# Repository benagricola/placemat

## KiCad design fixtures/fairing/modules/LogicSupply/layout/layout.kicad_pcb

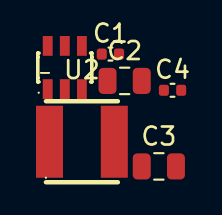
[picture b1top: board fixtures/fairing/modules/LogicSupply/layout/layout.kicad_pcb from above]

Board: 2 copper layers, 6 parts (0 on the bottom side), 5 nets, no tracks yet.

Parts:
C1, C4: GCM155R71H104KE02D; C_0402_1005Metric
C2: GMC21X5R106M50NT; C_0805_2012Metric
C3: CL21A226MOQNNNE; C_0805_2012Metric
U1: AP63203WU-7; TSOT-26_L2.9-W1.6-P0.95-LS2.8-BL
U2: SMNR4020-2.2UH; IND-SMD_L4.0-W4.0_LQH44PN2R2MP0L

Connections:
BST_3V3: C4.1, U1.6
GND: C1.2, C2.2, C3.2, U1.4
SW_3V3: C4.2, U1.5, U2.1
V3V3: C3.1, U1.1, U2.2
VSHUNT: C1.1, C2.1, U1.2, U1.3

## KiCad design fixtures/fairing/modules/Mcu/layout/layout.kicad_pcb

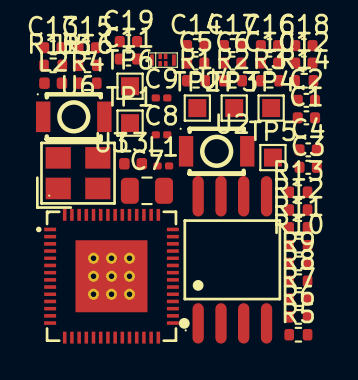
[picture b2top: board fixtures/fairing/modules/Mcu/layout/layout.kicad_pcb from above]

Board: 2 copper layers, 50 parts (0 on the bottom side), 32 nets, no tracks yet.

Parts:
C1, C2, C3: 1pF 50V C0G; C_0402_1005Metric
C4, C6, C10, C12, C13, C17: GCM155R71H104KE02D; C_0402_1005Metric
C5, C11, C14, C16: CL05A105KO5NNND; C_0402_1005Metric
C7: GRM21BC81E106KE51L; C_0805_2012Metric
C8, C9: GRM0335C2A1R5CA01D; C_0201_0603Metric
C15: GCM155R71H103KA55D; C_0402_1005Metric
C18, C19: GCM1555C1H160JA16D; C_0402_1005Metric
L1: 2.4nH; L_0201_0603Metric
L2: LQG15HS2N0S02D; L_0402_1005Metric
L3: 24nH; L_0402_1005Metric
R1, R4, R6, R7, R9, R10: ERJ-2GE0R00X; R_0402_1005Metric
R2, R3, R5, R8, R11, R12, R13, R14, R15: ERJ-2RKF1002X; R_0402_1005Metric
R16: ERJ-2RKF4990X; R_0402_1005Metric
TP1, TP2, TP3, TP4, TP5, TP6: ?; TestPoint_Pad_1.0x1.0mm
U1: ANT016008LCS2442MA1; ANT-SMD_6P-L1.6-W0.8-P1.20-1
U2: W25Q64JVSSIQ; SOIC-8_L5_3-W5_3-P1_27-LS8_0-BL
U3: ESP32-S3R8; QFN-56_L7_0-W7_0-P0_40-TL-EP4_0
U4, U5: B3U-1000P; KEY-SMD_B3U-1000PM
U6: S3240000101040; CRYSTAL-SMD_4P-L3_2-W2_5-BL

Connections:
ANT24_FEED: C3.1, R1.2, U1.4
ANT24_RAD: C1.1, U1.1
BOOT_STRAP: R2.2, TP2.1, U3.5, U4.1
FLASH_CLK: R4.2, U2.6
FLASH_CLK_CHIP: R4.1, U3.33
FLASH_CS: R5.2, U2.1, U3.32
FLASH_D: R6.2, U2.5
FLASH_D_CHIP: R6.1, U3.35
FLASH_HD: R7.2, R8.2, U2.7
FLASH_HD_CHIP: R7.1, U3.30
FLASH_Q: R9.2, U2.2
FLASH_Q_CHIP: R9.1, U3.34
FLASH_WP: R10.2, R11.2, U2.3
FLASH_WP_CHIP: R10.1, U3.31
GND: C1.2, C2.2, C3.2, C4.2, C5.2, C6.2, C7.2, C8.2, C9.2, C10.2, C11.2, C12.2, C13.2, C14.2, C15.2, C16.2, C17.2, C18.2, C19.2, R12.2, R14.2, R15.2, TP3.1, U2.4, U3.57, U4.2, U5.2, U6.2, U6.4
MCU_EN: C5.1, R3.2, TP4.1, U3.4, U5.1
RF_50: C2.1, C8.1, L1.2, R1.1
RF_CHIP: C9.1, L1.1, U3.1
SLOT_RUN: R12.1, U3.11
STRAP_DOWNLOAD: R15.1, U3.52
STRAP_JTAG: R13.2, U3.8
STRAP_VSPI: R14.1, U3.51
UART_RX: TP5.1, U3.50
UART_TX: R16.2, TP6.1
UART_TX_CHIP: R16.1, U3.49
V3V3: C4.1, C7.1, C11.1, C12.1, C13.1, C14.1, C15.1, L2.1, R2.1, R3.1, R13.1, TP1.1, U3.20, U3.46, U3.55, U3.56
VDD_RF: C10.1, L2.2, U3.2, U3.3
VDD_SPI: C6.1, C16.1, C17.1, R5.1, R8.1, R11.1, U2.8, U3.29
XTAL_1: C18.1, L3.2, U6.1
XTAL_N: C19.1, U3.53, U6.3
XTAL_P: L3.1, U3.54
ant24.Dummy_pad: U1.2, U1.3, U1.5, U1.6

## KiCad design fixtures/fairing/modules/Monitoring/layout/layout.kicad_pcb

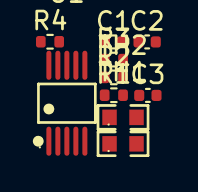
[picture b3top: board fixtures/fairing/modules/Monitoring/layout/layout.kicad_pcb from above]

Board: 2 copper layers, 10 parts (0 on the bottom side), 6 nets, no tracks yet.

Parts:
C1, C2, C3: GCM155R71H104KE02D; C_0402_1005Metric
R1, R3: ERJ-2RKF4702X; R_0402_1005Metric
R2, R4: ERJ-2RKF1001X; R_0402_1005Metric
TH1, TH2: NCU18XH103F60RB; R0603
U1: ADS1115IDGSR; MSOP-10_L3_0-W3_0-P0_50-LS5_0-BL

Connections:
ADC_BUCK: C2.1, R2.2, U1.6
ADC_PD: C3.1, R4.2, U1.7
GND: C1.2, C2.2, C3.2, TH1.2, TH2.2, U1.3
NTC_BUCK: R1.2, R2.1, TH1.1
NTC_PD: R3.2, R4.1, TH2.1
V3V3: C1.1, R1.1, R3.1, U1.1, U1.8

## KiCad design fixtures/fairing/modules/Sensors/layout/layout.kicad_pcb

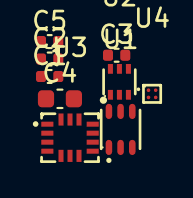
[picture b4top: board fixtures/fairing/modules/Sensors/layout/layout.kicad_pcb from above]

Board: 2 copper layers, 9 parts (0 on the bottom side), 4 nets, no tracks yet.

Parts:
C1, C2, C3, C5: GCM155R71H104KE02D; C_0402_1005Metric
C4: CL10A475KO8NNNC; C_0603_1608Metric
U1: LTR-303ALS-01; TDFN-6_L2.0-W2.0-P0.65-BL
U2: TMP102AIDRLR(UMW); SOT-563_L1.6-W1.2-P0.50-LS1.6-BL
U3: LSM6DS3TR-C; LGA-14_L3.0-W2.5-P0.50-TL
U4: MMC5603NJ; FLIPCHIP-4_L0.8-W0.8-R2-C2-P0.40-TL

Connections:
GND: C1.2, C2.2, C3.2, C4.2, C5.2, U1.3, U2.2, U2.4, U3.1, U3.2, U3.3, U3.6, U3.7, U4.A1
SCL: U1.4, U3.13, U4.A2
SDA: U1.6, U3.14, U4.B2
V3V3: C1.1, C2.1, C3.1, C4.1, C5.1, U1.1, U2.5, U3.5, U3.8, U3.12, U4.B1

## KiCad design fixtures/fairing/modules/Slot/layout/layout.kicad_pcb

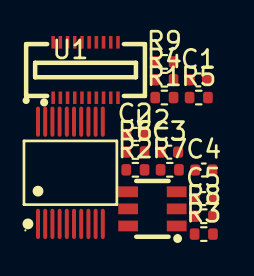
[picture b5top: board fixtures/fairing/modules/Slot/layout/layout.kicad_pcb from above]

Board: 2 copper layers, 17 parts (0 on the bottom side), 15 nets, no tracks yet.

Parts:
C1: GCM1555C1H102FA16D; C_0402_1005Metric
C2, C4: CL05A105KO5NNND; C_0402_1005Metric
C3, C5: GCM155R71H104KE02D; C_0402_1005Metric
J1: DF40C-20DS-0.4V(51); CONN-SMD_20P-P0_40_DF40C-20DS-0_4V
R1, R2, R3, R4, R8, R9: ERJ-2RKF1002X; R_0402_1005Metric
R5, R6: ERJ-2RKF1003X; R_0402_1005Metric
R7: ERJ-2RKF1303X; R_0402_1005Metric
U1: SN74CB3Q3245DGVR; TVSOP-20_L5_0-W4_4-P0_40-LS6_6-BL
U2: TPS2553DBVR; SOT-23-6_L2_9-W1_6-P0_95-LS2_8-BR

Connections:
ENABLE: R3.1, U2.3
FAULT_N: R4.2, U2.4
GND: C1.2, C2.2, C3.2, C4.2, C5.2, J1.3, J1.4, J1.6, J1.8, J1.10, J1.12, J1.14, J1.16, R2.2, R3.2, R7.2, U1.10, U2.2
ID_SENSE: C1.1, R6.2
ILIM: R7.1, U2.5
IRQ_N: R8.2, U1.6
OE_N: R9.2, U1.19
SLOT_3V3: C4.1, C5.1, J1.1, J1.2, R1.1, R2.1, U2.6
SLOT_CS_N: J1.11, R1.2, U1.15
SLOT_ID: J1.15, R5.2, R6.1
SLOT_IRQ_N: J1.13, U1.14
SLOT_MISO: J1.9, U1.16
SLOT_MOSI: J1.7, U1.17
SLOT_SCK: J1.5, U1.18
V3V3: C2.1, C3.1, R4.1, R8.1, R9.1, U1.20, U2.1

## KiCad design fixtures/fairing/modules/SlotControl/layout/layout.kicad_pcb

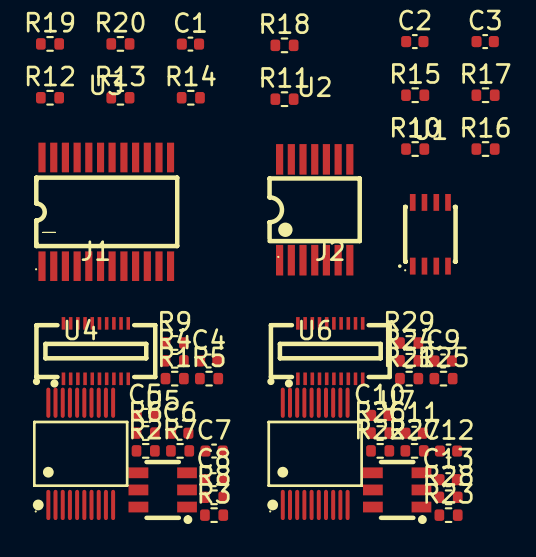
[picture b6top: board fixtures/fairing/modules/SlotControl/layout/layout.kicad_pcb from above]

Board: 2 copper layers, 51 parts (0 on the bottom side), 44 nets, no tracks yet.

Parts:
C1, C2, C3, C6, C8, C11, C13: GCM155R71H104KE02D; C_0402_1005Metric
C4, C9: GCM1555C1H102FA16D; C_0402_1005Metric
C5, C7, C10, C12: CL05A105KO5NNND; C_0402_1005Metric
J1, J2: DF40C-20DS-0.4V(51); CONN-SMD_20P-P0_40_DF40C-20DS-0_4V
R1, R2, R3, R4, R8, R9, R10, R11, R12, R15, R19, R21, R22, R23, R24, R28, R29: ERJ-2RKF1002X; R_0402_1005Metric
R5, R6, R25, R26: ERJ-2RKF1003X; R_0402_1005Metric
R7, R27: ERJ-2RKF1303X; R_0402_1005Metric
R13, R14, R16, R17, R18, R20: ERJ-2RKF2201X; R_0402_1005Metric
U1: SN74LVC2G00DCTR; SSOP-8_L3_0-W2_8-P0_65-LS4_0-BL-1
U2: SN74LVC08APWR; TSSOP-14_L5_0-W4_4-P0_65-LS6_4-BL
U3: TCA9555PWR; TSSOP-24_L7_8-W4_4-P0_65-LS6_4-BL
U4, U6: SN74CB3Q3245DGVR; TVSOP-20_L5_0-W4_4-P0_40-LS6_6-BL
U5, U7: TPS2553DBVR; SOT-23-6_L2_9-W1_6-P0_95-LS2_8-BR

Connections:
BB_FAULT: R11.2, U3.16
GND: C1.2, C2.2, C3.2, C4.2, C5.2, C6.2, C7.2, C8.2, C9.2, C10.2, C11.2, C12.2, C13.2, J1.3, J1.4, J1.6, J1.8, J1.10, J1.12, J1.14, J1.16, J2.3, J2.4, J2.6, J2.8, J2.10, J2.12, J2.14, J2.16, R2.2, R3.2, R7.2, R13.2, R14.2, R16.2, R17.2, R18.2, R20.2, R22.2, R23.2, R27.2, U1.4, U2.7, U3.12, U4.10, U5.2, U6.10, U7.2
HP_FAULT: R12.2, U3.19
HP_REQ: R13.1, U2.10, U3.8
ID_DRIVE: R5.1, R25.1, U2.11
ID_LEFT: C4.1, R6.2
ID_PROBE_REQ: R17.1, U2.13, U3.9
ID_RIGHT: C9.1, R26.2
INA_ALERT: R10.2, U3.1
LEFT_DATA_REQ: R14.1, U1.2, U3.6
LEFT_ENABLE: R3.1, U1.1, U2.3, U5.3
LEFT_FAULT_N: R4.2, U3.10, U5.4
LEFT_IRQ_N: R8.2, U3.13, U4.6
LEFT_OE_N: R9.2, U1.7, U4.19
LEFT_POWER_REQ: R16.1, U2.2, U3.4
RIGHT_DATA_REQ: R18.1, U1.6, U3.7
RIGHT_ENABLE: R23.1, U1.5, U2.6, U7.3
RIGHT_FAULT_N: R24.2, U3.11, U7.4
RIGHT_IRQ_N: R28.2, U3.14, U6.6
RIGHT_OE_N: R29.2, U1.3, U6.19
RIGHT_POWER_REQ: R20.1, U2.5, U3.5
SLOT_L_CS: R15.2, U4.5
SLOT_MISO: U4.4, U6.4
SLOT_MOSI: U4.3, U6.3
SLOT_RUN: U2.1, U2.4, U2.9, U2.12
SLOT_R_CS: R19.2, U6.5
SLOT_SCK: U4.2, U6.2
V3V3: C1.1, C2.1, C3.1, C5.1, C6.1, C10.1, C11.1, R4.1, R8.1, R9.1, R10.1, R11.1, R12.1, R15.1, R19.1, R24.1, R28.1, R29.1, U1.8, U2.14, U3.2, U3.3, U3.21, U3.24, U4.20, U5.1, U6.20, U7.1
left.ILIM: R7.1, U5.5
left.SLOT_3V3: C7.1, C8.1, J1.1, J1.2, R1.1, R2.1, U5.6
left.SLOT_CS_N: J1.11, R1.2, U4.15
left.SLOT_ID: J1.15, R5.2, R6.1
left.SLOT_IRQ_N: J1.13, U4.14
left.SLOT_MISO: J1.9, U4.16
left.SLOT_MOSI: J1.7, U4.17
left.SLOT_SCK: J1.5, U4.18
right.ILIM: R27.1, U7.5
right.SLOT_3V3: C12.1, C13.1, J2.1, J2.2, R21.1, R22.1, U7.6
right.SLOT_CS_N: J2.11, R21.2, U6.15
right.SLOT_ID: J2.15, R25.2, R26.1
right.SLOT_IRQ_N: J2.13, U6.14
right.SLOT_MISO: J2.9, U6.16
right.SLOT_MOSI: J2.7, U6.17
right.SLOT_SCK: J2.5, U6.18
